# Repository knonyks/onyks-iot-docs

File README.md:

# ONYKS IoT - Dokumentacja

## 14.11.2024

### Z czego korzystamy

- moduł [ESP32-WROOM-32D](https://www.espressif.com/sites/default/files/documentation/esp32-wroom-32d_esp32-wroom-32u_datasheet_en.pdf)
- program [KiCAD](https://www.kicad.org/) w wersji 8
- GitHub do przechowywania projektów

### Co zrobić do następnego spotkania

- zastanowić się jak ma działać urządzenie
- znaleźć główne peryferia spełniajace założenia projektu
- zaplanowanie maksymalnego poboru prądu przez dobrane peryferia
  - nie projektujemy jeszcze układu zasilania
- opcjonalnie: mały schemat w [drawio](https://app.diagrams.net/)
- zapoznać się z przykładowym devbardem

### Gdzie czytać

- oficjalny [devboard](https://docs.espressif.com/projects/esp-dev-kits/en/latest/esp32/esp32-devkitc/user_guide.html) - warto zapoznać się
  - na dole jest dokumentacja: specyfikacja techniczna, schematy, płytka PCB
- wprowadzenie do [KiCADa](https://docs.kicad.org/8.0/en/getting_started_in_kicad/getting_started_in_kicad.html)
- na przyszłość, można czytać w wolnej chwili [wprowadzenie do ESP32](https://docs.espressif.com/projects/esp-idf/en/v5.3.1/esp32/get-started/index.html)

### Podstawowe założenia

- zasilanie 3,3 V
- komunikacja Bluetooth (na tym etapie projektu to tylko ciekawostka)
- nie będzie programatora na płytce (programatory będą osobno)
- interfejsy UART i JTAG do programowania i debuggowania
- przycisk "reset"

### Components

- LDO: SOT-23-5 (DYD) [TLV75733PDBVR](https://www.ti.com/lit/ds/symlink/tlv757p.pdf?ts=1733149199380&ref_url=https%253A%252F%252Fwww.ti.com%252Fproduct%252FTLV757P%252Fpart-details%252FTLV75710PDBVR)
- NPN: SOT-23-3 [SS8050](https://www.micros.com.pl/mediaserver/TSS8050_BORN_0001.pdf)
- LED: 5050 [WS2812B](https://cdn-shop.adafruit.com/datasheets/WS2812B.pdf)
- Buttons: [6x3.5mm](https://pl.aliexpress.com/item/4000546183248.html?spm=a2g0o.order_list.order_list_main.169.6deb1c24ZkOZZl&gatewayAdapt=glo2pol) np. `Button_Switch_SMD:SW_Tactile_SPST_NO_Straight_CK_PTS636Sx25SMTRLFS`

### Connectors

- UART for programming
  - `Conn_01x06_Pin`
  - `Connector_PinHeader_2.54mm:PinHeader_1x06_P2.54mm_Vertical`
    1. VCC (3.3V)
    2. GND
    3. TXD (UART Transmit)
    4. RXD (UART Receive)
    5. DTR
    6. RTS

- JTAG for debugging (TMS, TCK, TDI, TDO, GND)
  - `Conn_02x05_Odd_Even`
  - `Connector_PinHeader_2.54mm:PinHeader_2x05_P2.54mm_Vertical`

- UART for communication
    1. GND
    2. TXD (UART Transmit)
    3. RXD (UART Receive)

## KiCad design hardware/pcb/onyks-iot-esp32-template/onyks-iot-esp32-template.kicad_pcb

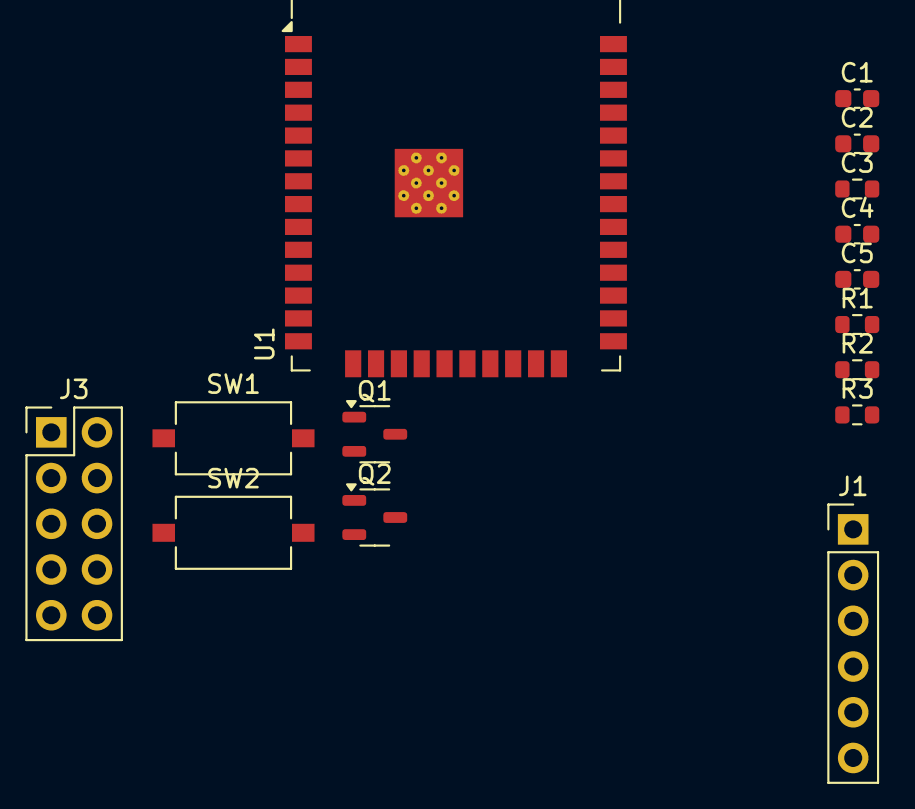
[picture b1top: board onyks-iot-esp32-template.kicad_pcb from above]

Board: 2 copper layers, 15 parts (0 on the bottom side), 9 nets, no tracks yet.

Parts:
C1: 22uF; C_0603_1608Metric
C2: 0.1uF; C_0603_1608Metric
C3: C; R_0603_1608Metric
C4, C5: 10uF; C_0603_1608Metric
J1: Conn_01x06_Pin; PinHeader_1x06_P2.54mm_Vertical
J3: JTAG; PinHeader_2x05_P2.54mm_Vertical
Q1, Q2: SS8050; SOT-23-3
R1: R; R_0603_1608Metric
R2, R3: 10k; R_0603_1608Metric
SW1: BOOT; SW_Tactile_SPST_NO_Straight_CK_PTS636Sx25SMTRLFS
SW2: RESET; SW_Tactile_SPST_NO_Straight_CK_PTS636Sx25SMTRLFS
U1: ESP32-WROOM-32D

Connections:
/MCU/DTR: J1.5, Q2.3 (E), R2.1
/MCU/EN: C3.1, C5.2, Q1.1 (C), R1.2, SW2.2, U1.3 (EN)
/MCU/IO0: C4.2, Q2.1 (C), SW1.2
/MCU/RTS: J1.6, Q1.3 (E), R3.1
GND: C1.2, C2.2, C3.2, C4.1, C5.1, J1.2, J3.3, J3.5, J3.9, SW1.1, SW2.1
unnamed: Q1.2 (B), R2.2
unnamed: Q2.2 (B), R3.2
unnamed: U1.1 (GND), U1.15 (GND), U1.38 (GND), U1.39 (GND)
VDD33: C1.1, C2.1, J1.1, J3.1, R1.1, U1.2 (VDD)

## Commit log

2024-11-14 Templates for pcb and placeholder for code
2024-11-14 0th - introduction
2024-11-14 Replaced 'USB' with 'UART' in README
2024-11-18 English version of README
2024-11-25 adding wrong file
2024-11-25 removing wrong file
2024-12-02 Components
2024-12-02 Connectors pinouts
2024-12-02 Uart communication
2024-12-02 DTR and RTS instead of EN and BOOT
2024-12-09 WIP: Template update
2025-07-23 pcb template: base project - WIP
